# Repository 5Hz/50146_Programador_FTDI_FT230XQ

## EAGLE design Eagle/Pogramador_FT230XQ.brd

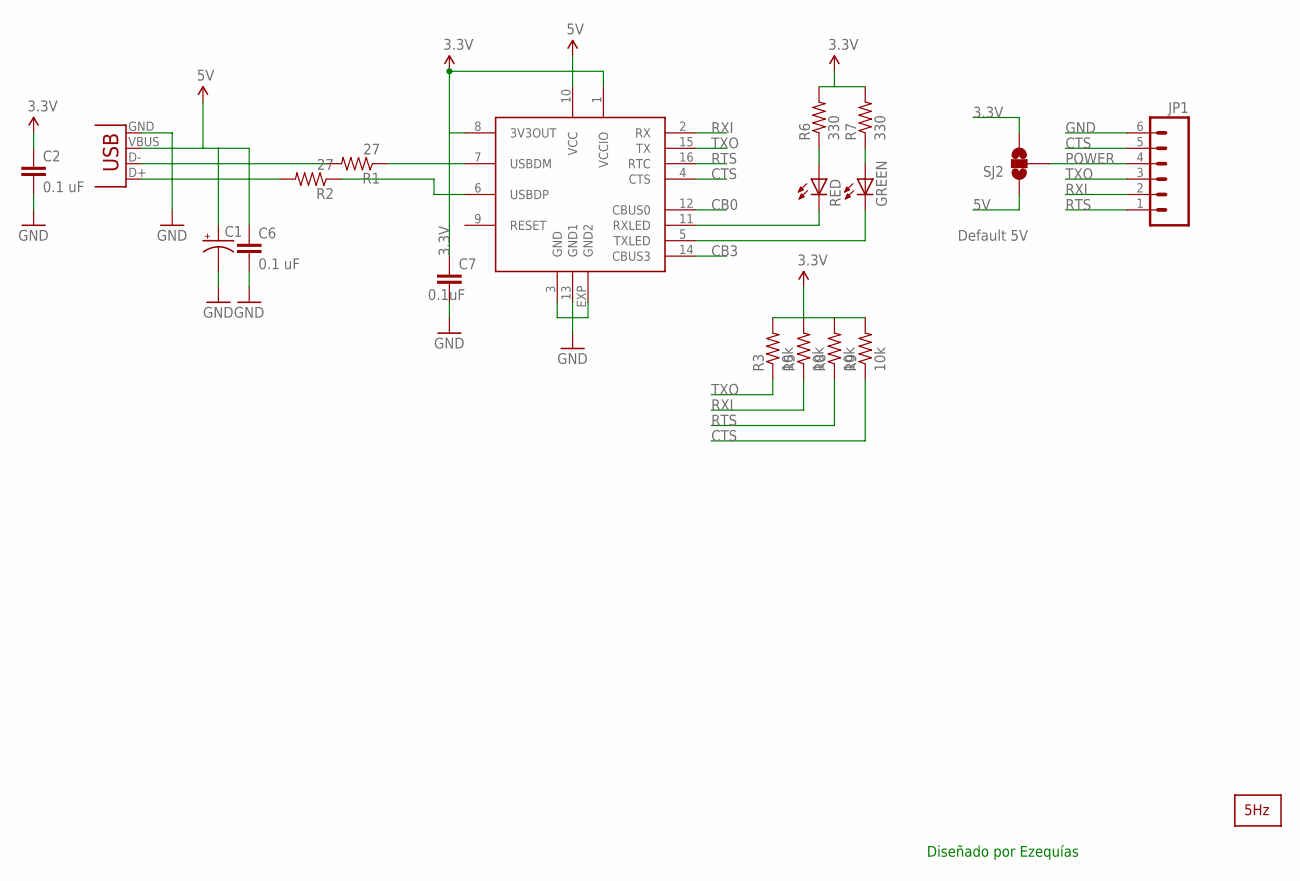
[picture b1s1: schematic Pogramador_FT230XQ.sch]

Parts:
C1: CAP_POL1206; EIA3216
C2, C6: 0.1 uF; 0603-CAP
C7: 0.1uF; 0603-CAP
GREEN: LED0603; LED-0603
JP1: M06SIP; 1X06
R1, R2: 27; 0603-RES
R3, R5, R8, R9: 10k; 0603-RES
R6, R7: 330; 0603-RES
RED: LED0603; LED-0603
SJ2: SOLDERJUMPER_2WAYS; SJ_3
U$2: LOGO2_SILKL5MM; LARGO2_5MM
U$5: FT230; QFN-16
X1: USBSMD; USB-MINIB

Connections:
3.3V: C2.1, C7.1, R3.2, R5.2, R6.2, R7.2, R8.2, R9.2, SJ2.3, U$5.1 (VCCIO), U$5.8 (3V3OUT)
5V: C1.A (+), C6.1, SJ2.1, U$5.10 (VCC), X1.VBUS
CB0: U$5.12 (CBUS0)
CB3: U$5.14 (CBUS3)
CTS: JP1.5, R9.1, U$5.4 (CTS)
GND: C1.C (-), C2.2, C6.2, C7.2, JP1.6, U$5.3 (GND), U$5.13 (GND1), U$5.EXP (GND2), X1.GND
unnamed: R2.1, U$5.6 (USBDP)
unnamed: R1.1, U$5.7 (USBDM)
unnamed: R1.2, X1.D-
unnamed: R2.2, X1.D+
unnamed: GREEN.A, R7.1
unnamed: R6.1, RED.A
unnamed: RED.C, U$5.11 (RXLED)
unnamed: GREEN.C, U$5.5 (TXLED)
POWER: JP1.4, SJ2.2
RTS: JP1.1, R8.1, U$5.16 (RTC)
RXI: JP1.2, R5.1, U$5.2 (RX)
TXO: JP1.3, R3.1, U$5.15 (TX)

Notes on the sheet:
Default 5V
Diseñado por Ezequías

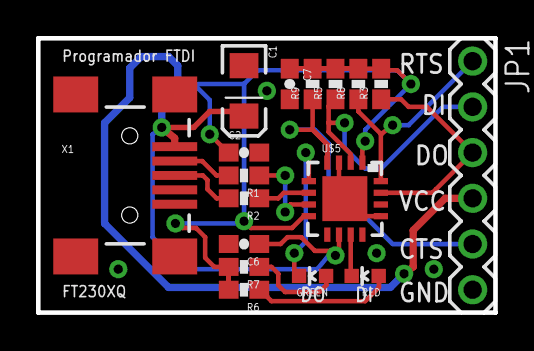
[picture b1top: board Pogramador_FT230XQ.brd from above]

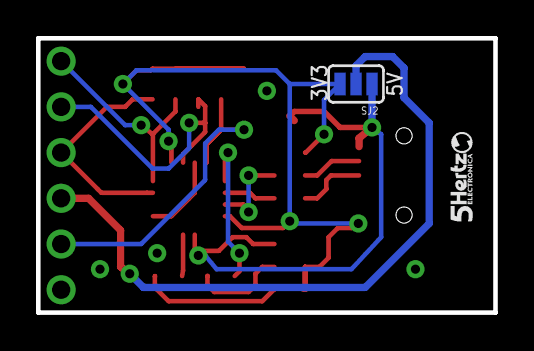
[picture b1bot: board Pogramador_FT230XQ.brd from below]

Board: 2 copper layers, 25.4 x 15.2 mm, 19 parts (2 on the bottom side), 16 nets.

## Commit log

2014-03-20 Creación
